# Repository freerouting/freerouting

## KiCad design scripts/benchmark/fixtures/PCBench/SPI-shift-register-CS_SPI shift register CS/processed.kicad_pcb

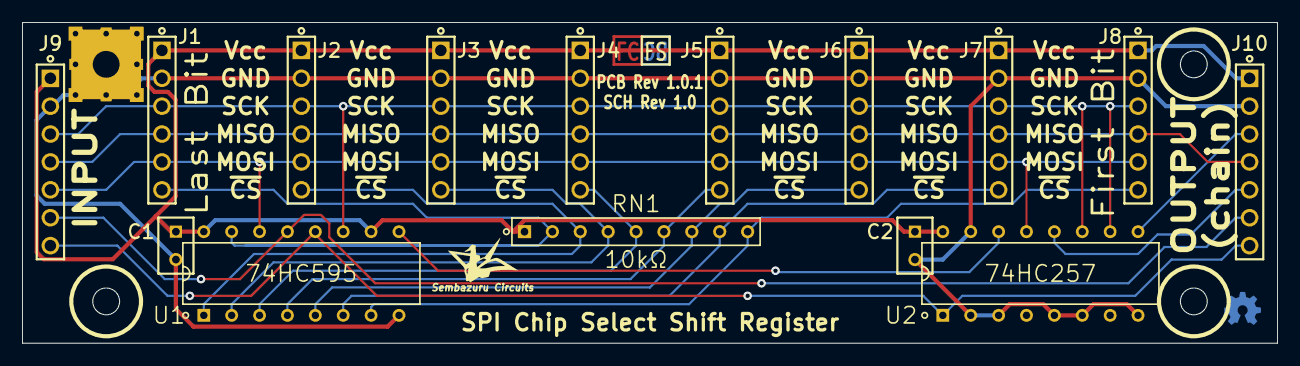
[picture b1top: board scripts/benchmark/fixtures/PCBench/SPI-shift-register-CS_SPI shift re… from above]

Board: 2 copper layers, 114.3 x 29.2 mm, 20 parts (0 on the bottom side), 18 nets.

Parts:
C1, C2: 0.1µF; CAPRR254W51L508T318H660P
J1, J2, J3, J4, J5, J6, J7, J8: CONN_06; HDRV6W64P254_1X6_1524X254X1016P
J9, J10: CONN_07; HDRV7W64P254_1X7_1778X254X1016P
LayerIcon02: VAL**; LayerIcon02
MH1: #2 Free Fit; MTGP635H244V8P
MH2, MH3, MH4: #2 Free Fit; MTGNP635H244Z635P
RN1: 10kΩ; SIP249W55P254L2261H495Q9C
U1: 74HC595; DIP762W52P254L2159H381Q16C
U2: 74HC257; DIP762W52P254L2159H381Q16C

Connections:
/MISO: J1.4, J2.4, J3.4, J4.4, J5.4, J6.4, J7.4, J8.4, J9.4, J10.4
/MOSI: J1.5, J2.5, J3.5, J4.5, J5.5, J6.5, J7.5, J8.5, J9.5, U1.14, U2.13
/MOSI/Ser: J10.5, U2.12
/SCK: J1.3, J2.3, J3.3, J4.3, J5.3, J6.3, J7.3, J8.3, J9.3, U1.11, U2.10, U2.11
/SCKdelayed: J10.3, U2.9
/SerChain: U1.9, U2.14
/~CS1: J1.6, RN1.2, U1.15
/~CS2: J2.6, RN1.3, U1.1
/~CS3: J3.6, RN1.4, U1.2
/~CS4: J4.6, RN1.5, U1.3
/~CS5: J5.6, RN1.6, U1.4
/~CS6: J6.6, RN1.7, U1.5
/~CS7: J7.6, RN1.8, U1.6
/~CS8: J8.6, RN1.9, U1.7
/~dCS: J9.6, J10.6, U1.13
/~rCS: J9.7, J10.7, U1.12, U2.1
GND: C1.2, C2.2, J1.2, J2.2, J3.2, J4.2, J5.2, J6.2, J7.2, J8.2, J9.2, J10.2, MH1.0, U1.8, U2.2, U2.3, U2.5, U2.6, U2.8, U2.15
VCC: C1.1, C2.1, J1.1, J2.1, J3.1, J4.1, J5.1, J6.1, J7.1, J8.1, J9.1, J10.1, RN1.1, U1.10, U1.16, U2.16

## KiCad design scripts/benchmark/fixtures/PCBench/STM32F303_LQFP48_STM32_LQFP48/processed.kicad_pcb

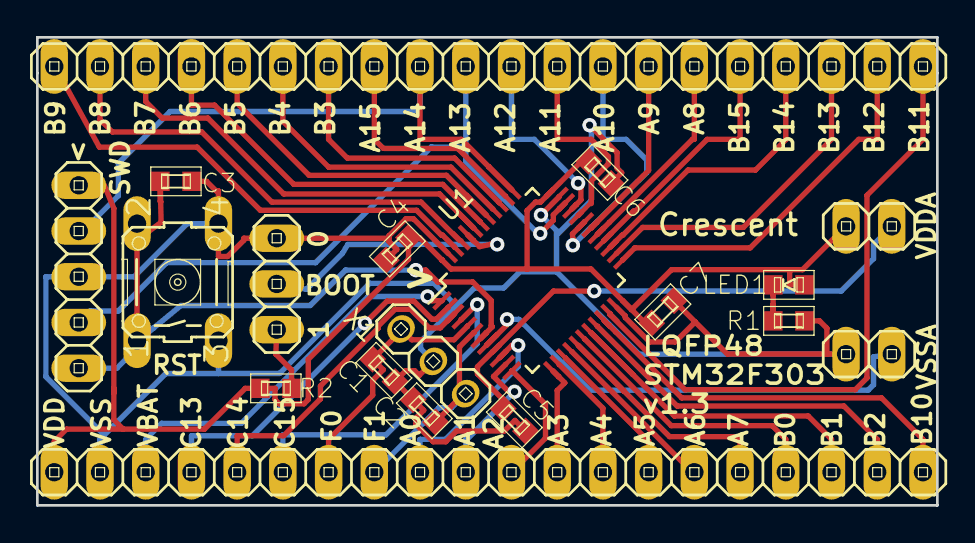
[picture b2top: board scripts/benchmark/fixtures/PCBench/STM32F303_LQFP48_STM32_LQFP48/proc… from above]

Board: 2 copper layers, 50.0 x 26.0 mm, 19 parts (0 on the bottom side), 46 nets.

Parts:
C1, C2, C3, C4, C5, C6, C7: CAPACITOR1608; generic-SMD1608
JP1: PINHD-1X5; pinhead-1X05
JP2: PINHD-1X3; pinhead-1X03
JP3, JP5: PINHD-1X2; pinhead-1X02
JP4, JP6: PINHD-1X20; pinhead-1X20
LED1: LED1608; generic-LED1608
R1, R2: RESISTOR1608; generic-SMD1608
S1: 10-XX; switch-omron-B3F-10XX
U1: STM32F100C8; LQFP-48_7x7mm_Pitch0.5mm
X1: CRYSTAL_SMD; pinhead-1X03

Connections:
BOOT: JP2.2, U1.44
NRST: C3.1, JP1.5, S1.1, S1.2, U1.7
unnamed: JP2.1, R2.2
unnamed: LED1.K, R1.1
OSCI: C1.1, JP4.7, U1.5, X1.1
OSCO: C2.1, JP4.8, U1.6, X1.2
PA0: JP4.9, U1.10
PA1: JP4.10, U1.11
PA2: JP4.11, U1.12
PA3: JP4.12, U1.13
PA4: JP4.13, U1.14
PA5: JP4.14, U1.15
PA6: JP4.15, U1.16
PA7: JP4.16, U1.17
PA8: JP6.15, U1.29
PA9: JP6.14, U1.30
PA10: JP6.13, U1.31
PA11: JP6.12, U1.32
PA12: JP6.11, U1.33
PA13: JP1.4, JP6.10, U1.34
PA14: JP1.2, JP6.9, U1.37
PA15: JP6.8, U1.38
PB0: JP4.17, U1.18
PB1: JP4.18, U1.19
PB2: JP4.19, U1.20
PB3: JP6.7, U1.39
PB4: JP6.6, U1.40
PB5: JP6.5, U1.41
PB6: JP6.4, U1.42
PB7: JP6.3, U1.43
PB8: JP6.2, U1.45
PB9: JP6.1, U1.46
PB10: JP4.20, U1.21
PB11: JP6.20, U1.22
PB12: JP6.19, U1.25
PB13: JP6.18, U1.26
PB14: JP6.17, U1.27
PB15: JP6.16, U1.28
PC13: JP4.4, U1.2
PC14: JP4.5, U1.3
PC15: JP4.6, U1.4
VBAT: JP4.3, U1.1
VDD: C4.1, C6.1, C7.1, JP1.1, JP3.1, JP4.1, LED1.A, R2.1, U1.24, U1.36, U1.48
VDDA: C5.1, JP3.2, U1.9
VSS: C1.2, C2.2, C3.2, C4.2, C5.2, C6.2, C7.2, JP1.3, JP2.3, JP4.2, JP5.1, R1.2, S1.3, S1.4, U1.23, U1.35, U1.47, X1.3
VSSA: JP5.2, U1.8
